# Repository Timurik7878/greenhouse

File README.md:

аааааааааааааааааааааааааааааааааааааааааааааааааааааааааааааааааыыыыыыыыыыыыыыыыыыыыыыыыыыыыыыыыыыыыыыыыыыыыыыыыыыыыыыыыыыыыыыыыыыыыыыыыыыааааааааааааааааааааааааааааааааааааааааааааааааааааыыыыыыыыыыыыыыыыыыыыыыыыыыввввввввввввввввввввыыыыыыыыыыыыыыыыыыыыаааааааааааааааавввввввввыыыыыыааааааааааааааывввффывавывввввввввввввввыыыыыыыыыыыыыыыыы
HelloWorld("print")

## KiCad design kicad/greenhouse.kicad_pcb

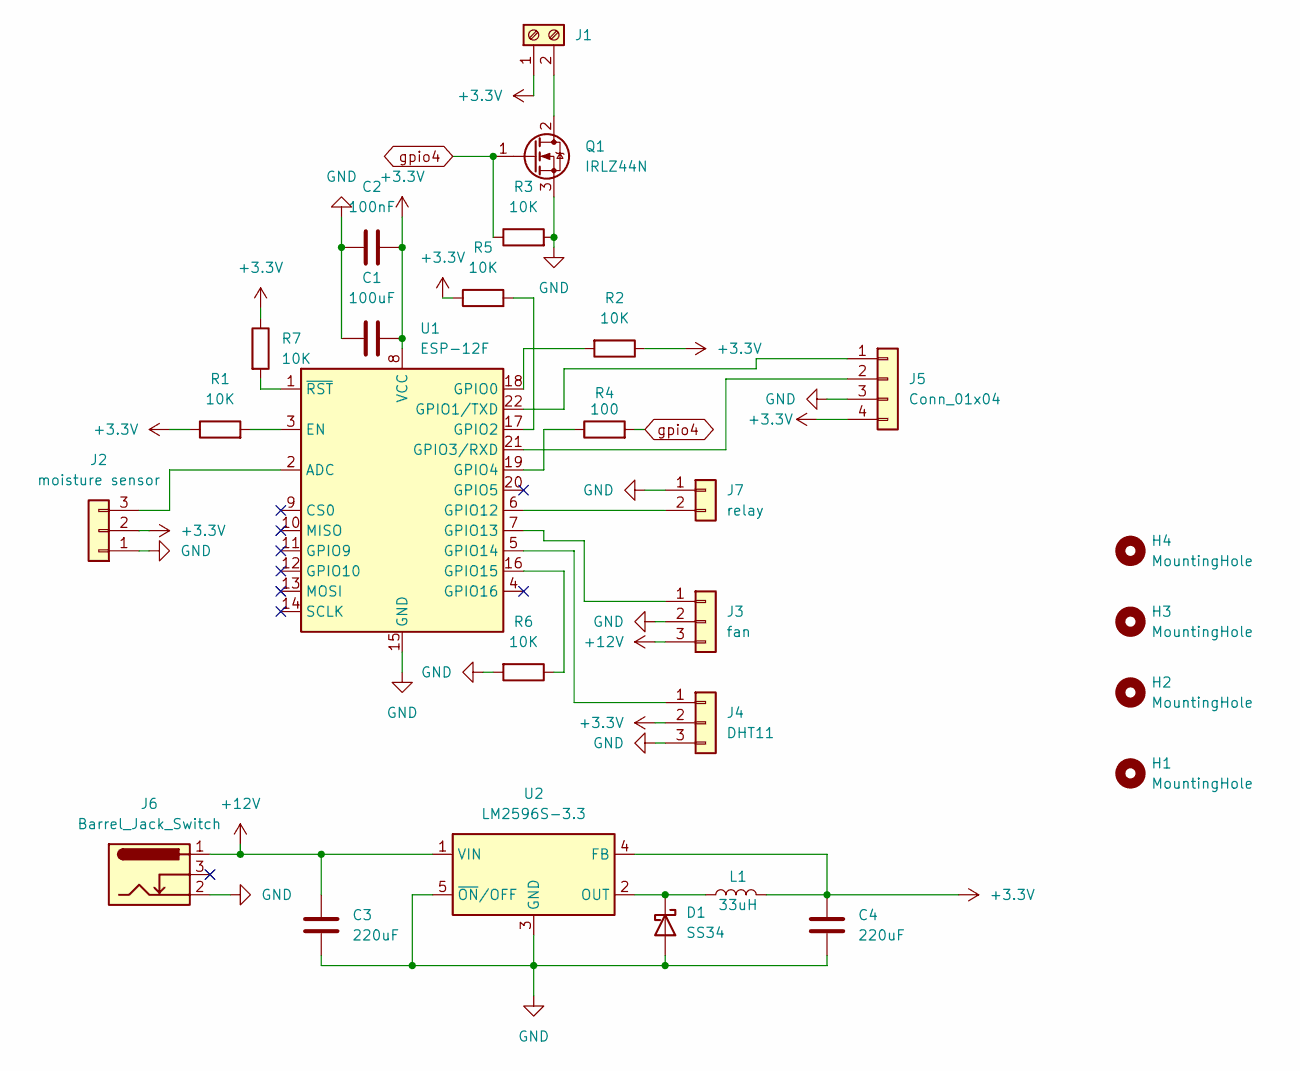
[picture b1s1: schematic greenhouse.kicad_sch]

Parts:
C1: 100uF; CP_Radial_D5.0mm_P2.00mm
C2: 100nF; C_Disc_D5.0mm_W2.5mm_P2.50mm
C3, C4: 220uF; CP_Radial_D5.0mm_P2.00mm
D1: SS34; D_SMA
H1, H2, H3, H4: MountingHole; MountingHole_2.2mm_M2_Pad
J1: Screw_Terminal_01x02; TerminalBlock_Phoenix_MKDS-3-2-5.08_1x02_P5.08mm_Horizontal
J2: moisture sensor; PinHeader_1x03_P2.54mm_Vertical
J3: fan; PinHeader_1x03_P2.54mm_Vertical
J4: DHT11; PinHeader_1x03_P2.54mm_Vertical
J5: Conn_01x04; PinHeader_1x04_P2.54mm_Vertical
J6: Barrel_Jack_Switch; BarrelJack_Horizontal
J7: relay; PinHeader_1x02_P2.54mm_Vertical
L1: 33uH; L_12x12mm_H8mm
Q1: IRLZ44N; TO-220-3_Vertical
R1, R2, R3, R5, R6, R7: 10K; R_0805_2012Metric_Pad1.20x1.40mm_HandSolder
R4: 100; R_0805_2012Metric_Pad1.20x1.40mm_HandSolder
U1: ESP-12F; ESP-12E
U2: LM2596S-3.3; TO-263-5_TabPin3

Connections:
+3.3V: C1.1, C2.1, C4.1, J1.1, J2.2, J4.2, J5.4, L1.2, R1.1, R2.1, R5.1, R7.1, U1.8 (VCC), U2.4 (FB)
+12V: C3.1, J3.3, J6.1, U2.1 (VIN)
GND: C1.2, C2.2, C3.2, C4.2, D1.2 (A), J2.1, J3.2, J4.3, J5.3, J6.2, J7.1, Q1.3 (S), R3.2, R6.2, U1.15 (GND), U2.3 (GND), U2.5 (~ON/OFF)
unnamed: D1.1 (K), L1.1, U2.2 (OUT)
unnamed: J1.2, Q1.2 (D)
unnamed: J2.3, U1.2 (ADC)
unnamed: J3.1, U1.7 (GPIO13)
unnamed: J4.1, U1.5 (GPIO14)
unnamed: J5.1, U1.22 (GPIO1/TXD)
unnamed: J5.2, U1.21 (GPIO3/RXD)
unnamed: J7.2, U1.6 (GPIO12)
unnamed: R1.2, U1.3 (EN)
unnamed: R2.2, U1.18 (GPIO0)
unnamed: R5.2, U1.17 (GPIO2)
unnamed: R4.1, U1.19 (GPIO4)
unnamed: R6.1, U1.16 (GPIO15)
unnamed: R7.2, U1.1 (~RST)
gpio4: Q1.1 (G), R3.1, R4.2

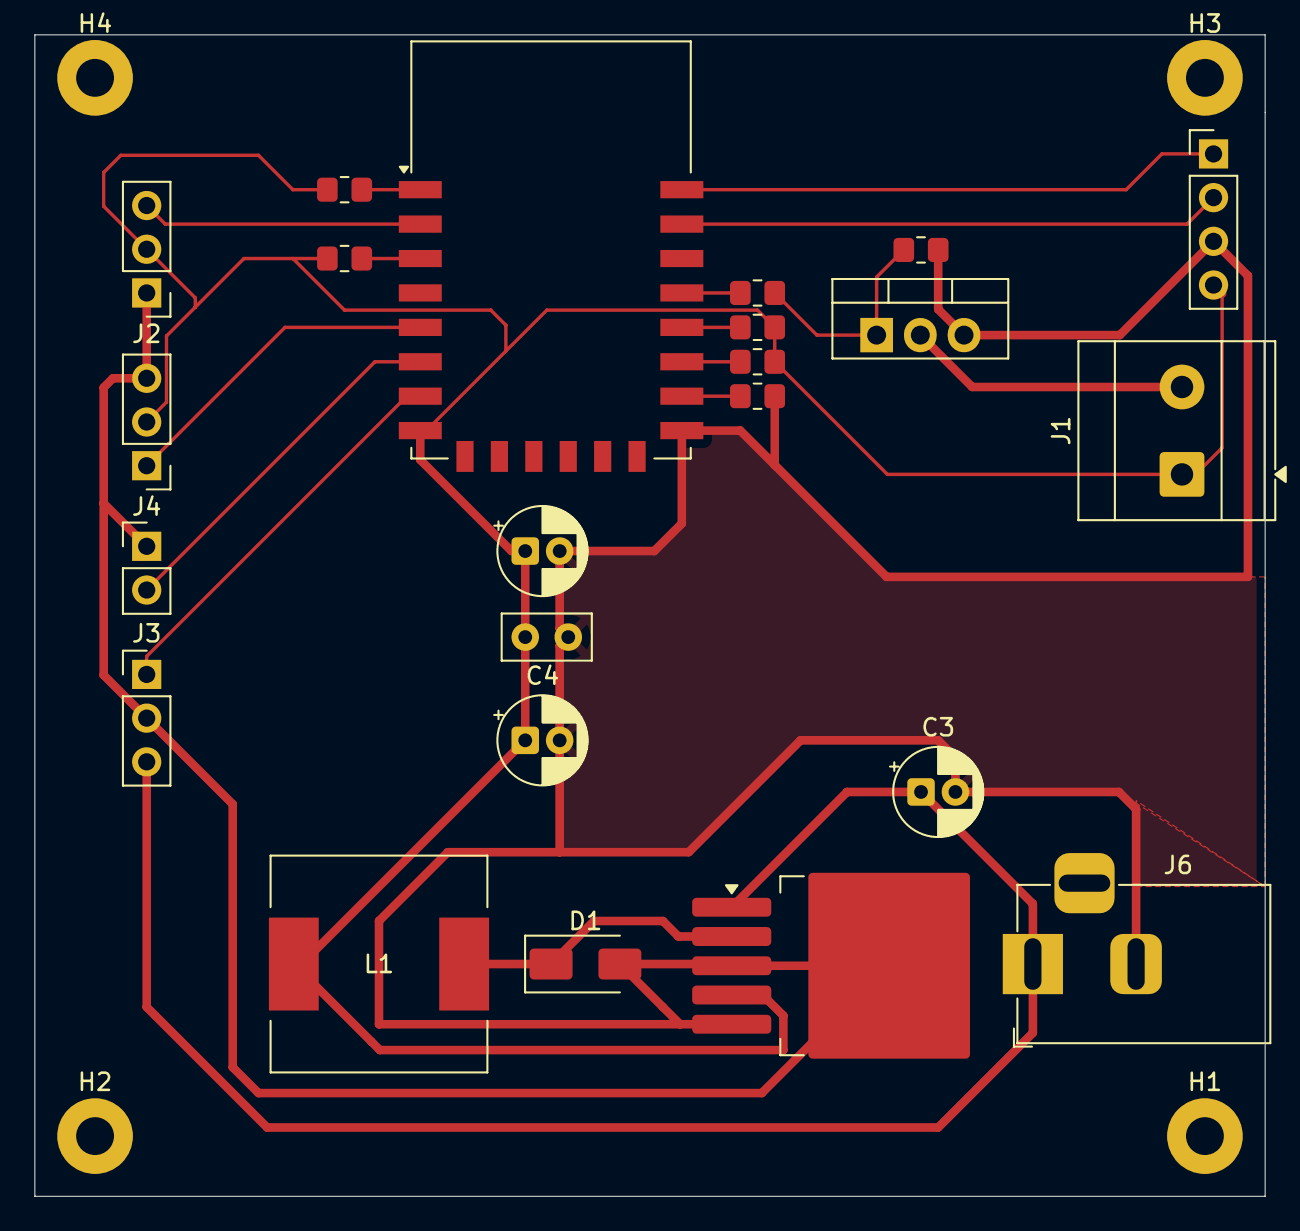
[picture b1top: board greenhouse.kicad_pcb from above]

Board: 2 copper layers, 71.5 x 67.5 mm, 27 parts (0 on the bottom side), 18 nets.

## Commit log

2026-03-08 greenhouse
    a
2026-04-02 ыыыыыыыыыыыыыыы
